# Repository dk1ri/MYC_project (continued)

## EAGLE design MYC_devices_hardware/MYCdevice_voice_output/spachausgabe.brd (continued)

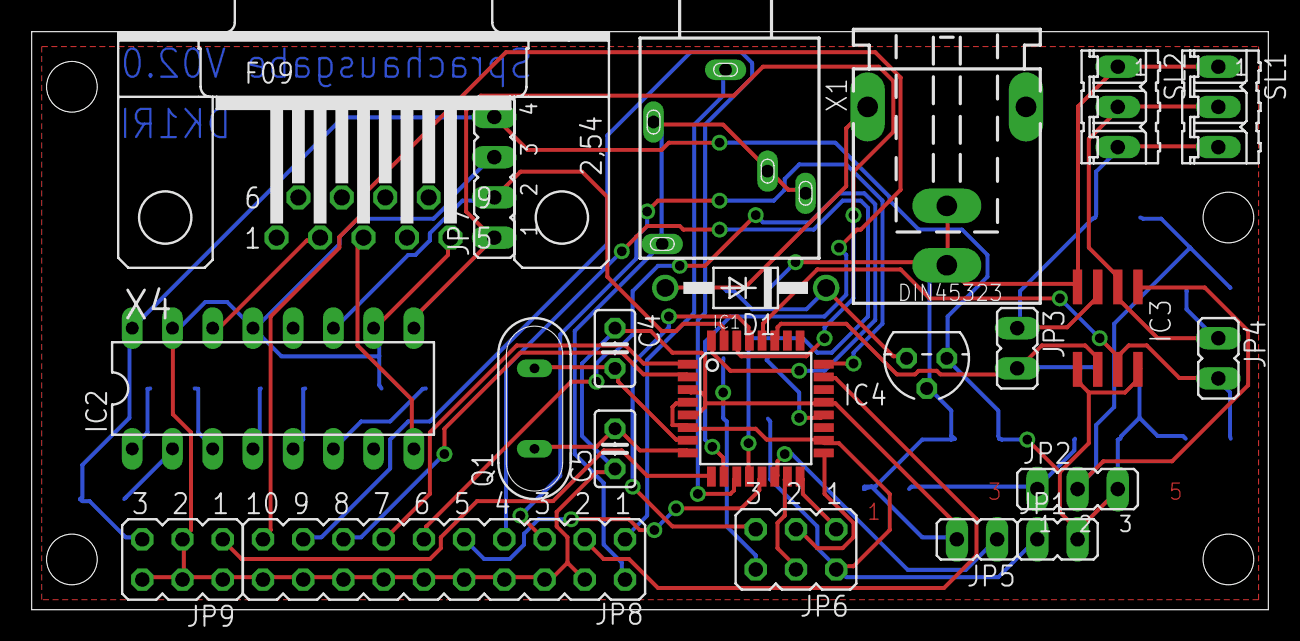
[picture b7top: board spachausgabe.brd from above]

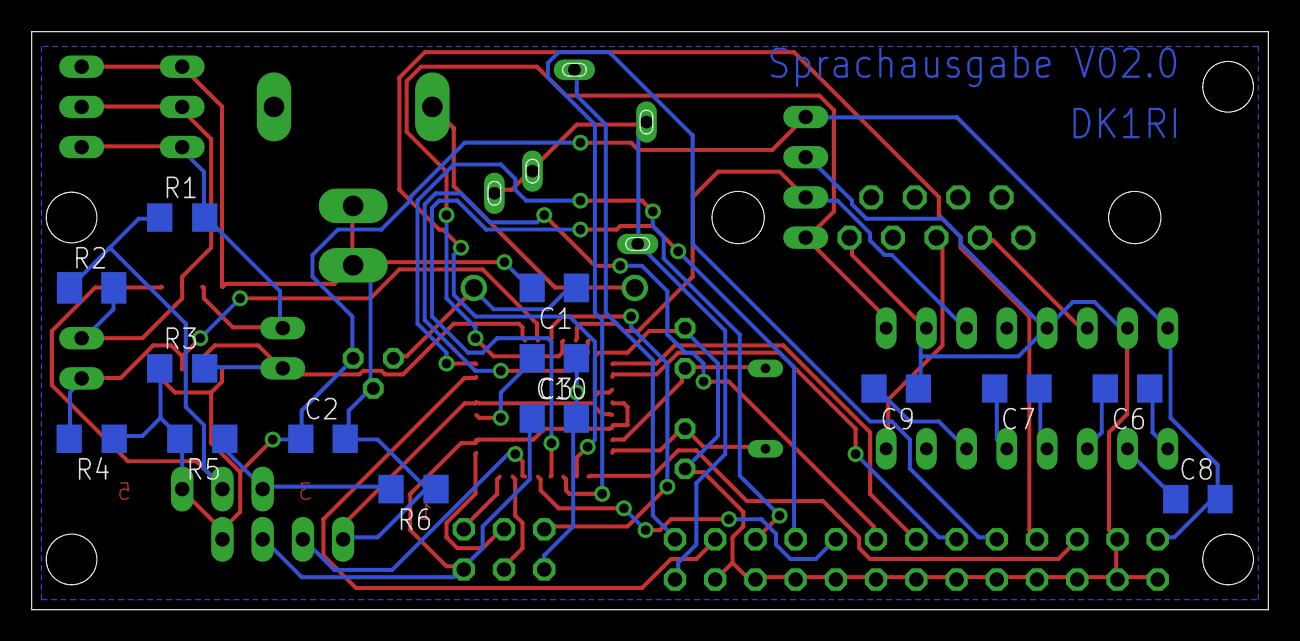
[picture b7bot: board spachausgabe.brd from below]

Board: 2 copper layers, 78.1 x 36.5 mm, 36 parts (14 on the bottom side), 41 nets.
